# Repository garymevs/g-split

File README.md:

# g-split
A 60%(ish) split keeb (Still waiting on a good name)

Current status: Procrastination
- [x] PCB design
- [x] Case design
- [x] PCB test fit with 3D printed parts
- [ ] Final case design 

Thankies [funkiwinter](https://twitch.tv/funkiwinter) for the cute goat <3

CAD stuff done with [Solid Edge](https://solidedge.siemens.com/en/) and [KiCad](https://www.kicad.org/) (+ other random utilities for hacky workarounds)

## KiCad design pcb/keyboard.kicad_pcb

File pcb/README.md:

# g-split
A 60%(ish) split keeb (Still waiting on a good name)

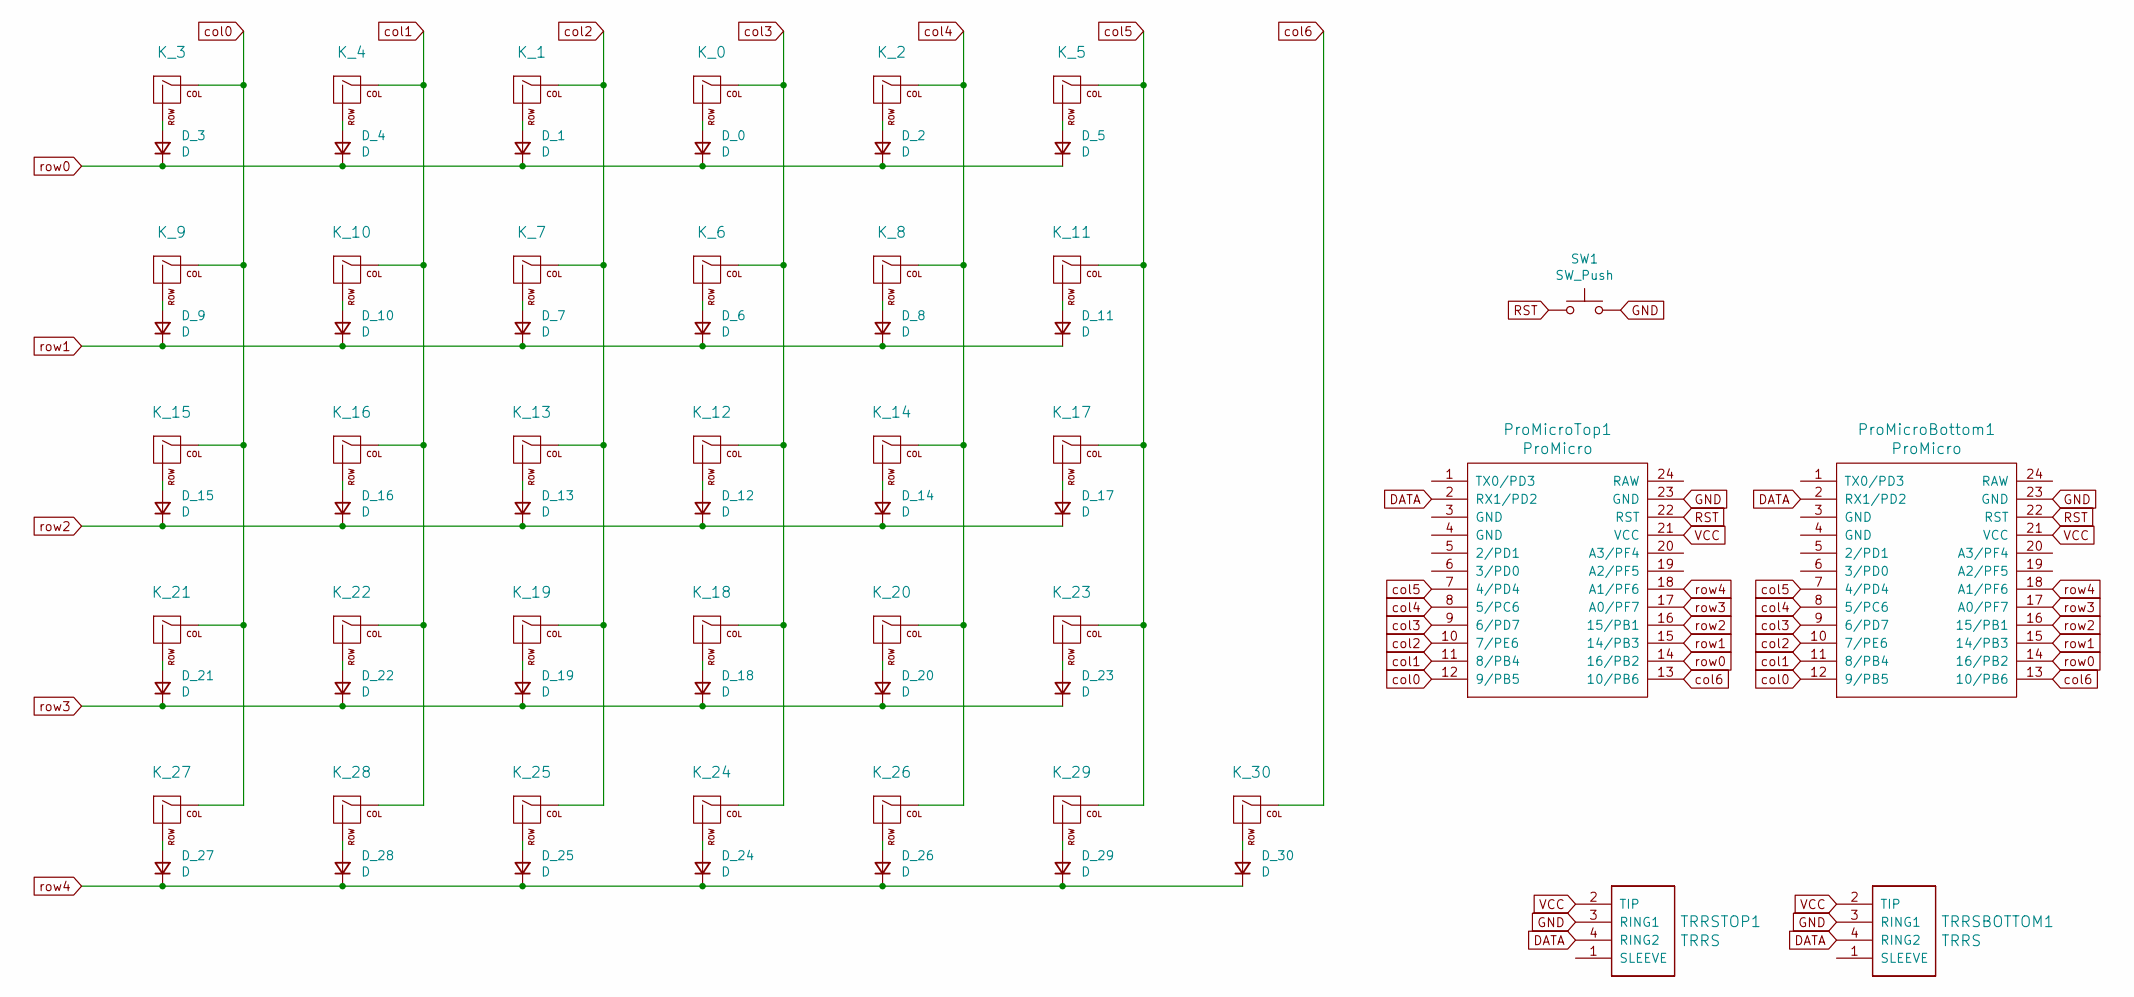
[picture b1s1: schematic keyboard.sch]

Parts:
D_0, D_1, D_2, D_3, D_4, D_5, D_6, D_7, D_8, D_9, D_10, D_11, D_12, D_13, D_14, D_15, D_16, D_17, D_18, D_19, D_20, D_21, D_22, D_23, D_24, D_25, D_26, D_27, D_28, D_29, D_30: D; D_SOD123_axial
K_0, K_1, K_2, K_3, K_4, K_5, K_6, K_7, K_8, K_9, K_10, K_11, K_12, K_13, K_14, K_15, K_16, K_17, K_18, K_19, K_20, K_21, K_22, K_23, K_24, K_25, K_26, K_27, K_28: KEYSW; ReinforcedKailhHotswap
K_29: KEYSW; ReinforcedKailhHotswap-2u-flipped-stab
K_30: KEYSW; ReinforcedKailhHotswap-2u
ProMicroBottom1: ProMicro; ArduinoProMicro
ProMicroTop1: ProMicro; ArduinoProMicro
SW1: SW_Push; SW_PUSH_6mm_H5mm
TRRSBOTTOM1: TRRS; TRRS-PJ-320A
TRRSTOP1: TRRS; TRRS-PJ-320A

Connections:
DATA: ProMicroBottom1.2 (RX1/PD2), ProMicroTop1.2 (RX1/PD2), TRRSBOTTOM1.4 (RING2), TRRSTOP1.4 (RING2)
GND: ProMicroBottom1.23 (GND), ProMicroTop1.23 (GND), SW1.2, TRRSBOTTOM1.3 (RING1), TRRSTOP1.3 (RING1)
unnamed: D_0.2 (A), K_0.2 (ROW)
unnamed: D_1.2 (A), K_1.2 (ROW)
unnamed: D_2.2 (A), K_2.2 (ROW)
unnamed: D_3.2 (A), K_3.2 (ROW)
unnamed: D_4.2 (A), K_4.2 (ROW)
unnamed: D_5.2 (A), K_5.2 (ROW)
unnamed: D_6.2 (A), K_6.2 (ROW)
unnamed: D_7.2 (A), K_7.2 (ROW)
unnamed: D_8.2 (A), K_8.2 (ROW)
unnamed: D_9.2 (A), K_9.2 (ROW)
unnamed: D_10.2 (A), K_10.2 (ROW)
unnamed: D_11.2 (A), K_11.2 (ROW)
unnamed: D_12.2 (A), K_12.2 (ROW)
unnamed: D_13.2 (A), K_13.2 (ROW)
unnamed: D_14.2 (A), K_14.2 (ROW)
unnamed: D_15.2 (A), K_15.2 (ROW)
unnamed: D_16.2 (A), K_16.2 (ROW)
unnamed: D_17.2 (A), K_17.2 (ROW)
unnamed: D_18.2 (A), K_18.2 (ROW)
unnamed: D_19.2 (A), K_19.2 (ROW)
unnamed: D_20.2 (A), K_20.2 (ROW)
unnamed: D_21.2 (A), K_21.2 (ROW)
unnamed: D_22.2 (A), K_22.2 (ROW)
unnamed: D_23.2 (A), K_23.2 (ROW)
unnamed: D_24.2 (A), K_24.2 (ROW)
unnamed: D_25.2 (A), K_25.2 (ROW)
unnamed: D_26.2 (A), K_26.2 (ROW)
unnamed: D_27.2 (A), K_27.2 (ROW)
unnamed: D_28.2 (A), K_28.2 (ROW)
unnamed: D_29.2 (A), K_29.2 (ROW)
unnamed: D_30.2 (A), K_30.2 (ROW)
RST: ProMicroBottom1.22 (RST), ProMicroTop1.22 (RST), SW1.1
VCC: ProMicroBottom1.21 (VCC), ProMicroTop1.21 (VCC), TRRSBOTTOM1.2 (TIP), TRRSTOP1.2 (TIP)
col0: K_3.1 (COL), K_9.1 (COL), K_15.1 (COL), K_21.1 (COL), K_27.1 (COL), ProMicroBottom1.12 (9/PB5), ProMicroTop1.12 (9/PB5)
col1: K_4.1 (COL), K_10.1 (COL), K_16.1 (COL), K_22.1 (COL), K_28.1 (COL), ProMicroBottom1.11 (8/PB4), ProMicroTop1.11 (8/PB4)
col2: K_1.1 (COL), K_7.1 (COL), K_13.1 (COL), K_19.1 (COL), K_25.1 (COL), ProMicroBottom1.10 (7/PE6), ProMicroTop1.10 (7/PE6)
col3: K_0.1 (COL), K_6.1 (COL), K_12.1 (COL), K_18.1 (COL), K_24.1 (COL), ProMicroBottom1.9 (6/PD7), ProMicroTop1.9 (6/PD7)
col4: K_2.1 (COL), K_8.1 (COL), K_14.1 (COL), K_20.1 (COL), K_26.1 (COL), ProMicroBottom1.8 (5/PC6), ProMicroTop1.8 (5/PC6)
col5: K_5.1 (COL), K_11.1 (COL), K_17.1 (COL), K_23.1 (COL), K_29.1 (COL), ProMicroBottom1.7 (4/PD4), ProMicroTop1.7 (4/PD4)
col6: K_30.1 (COL), ProMicroBottom1.13 (10/PB6), ProMicroTop1.13 (10/PB6)
row0: D_0.1 (K), D_1.1 (K), D_2.1 (K), D_3.1 (K), D_4.1 (K), D_5.1 (K), ProMicroBottom1.14 (16/PB2), ProMicroTop1.14 (16/PB2)
row1: D_6.1 (K), D_7.1 (K), D_8.1 (K), D_9.1 (K), D_10.1 (K), D_11.1 (K), ProMicroBottom1.15 (14/PB3), ProMicroTop1.15 (14/PB3)
row2: D_12.1 (K), D_13.1 (K), D_14.1 (K), D_15.1 (K), D_16.1 (K), D_17.1 (K), ProMicroBottom1.16 (15/PB1), ProMicroTop1.16 (15/PB1)
row3: D_18.1 (K), D_19.1 (K), D_20.1 (K), D_21.1 (K), D_22.1 (K), D_23.1 (K), ProMicroBottom1.17 (A0/PF7), ProMicroTop1.17 (A0/PF7)
row4: D_24.1 (K), D_25.1 (K), D_26.1 (K), D_27.1 (K), D_28.1 (K), D_29.1 (K), D_30.1 (K), ProMicroBottom1.18 (A1/PF6), ProMicroTop1.18 (A1/PF6)

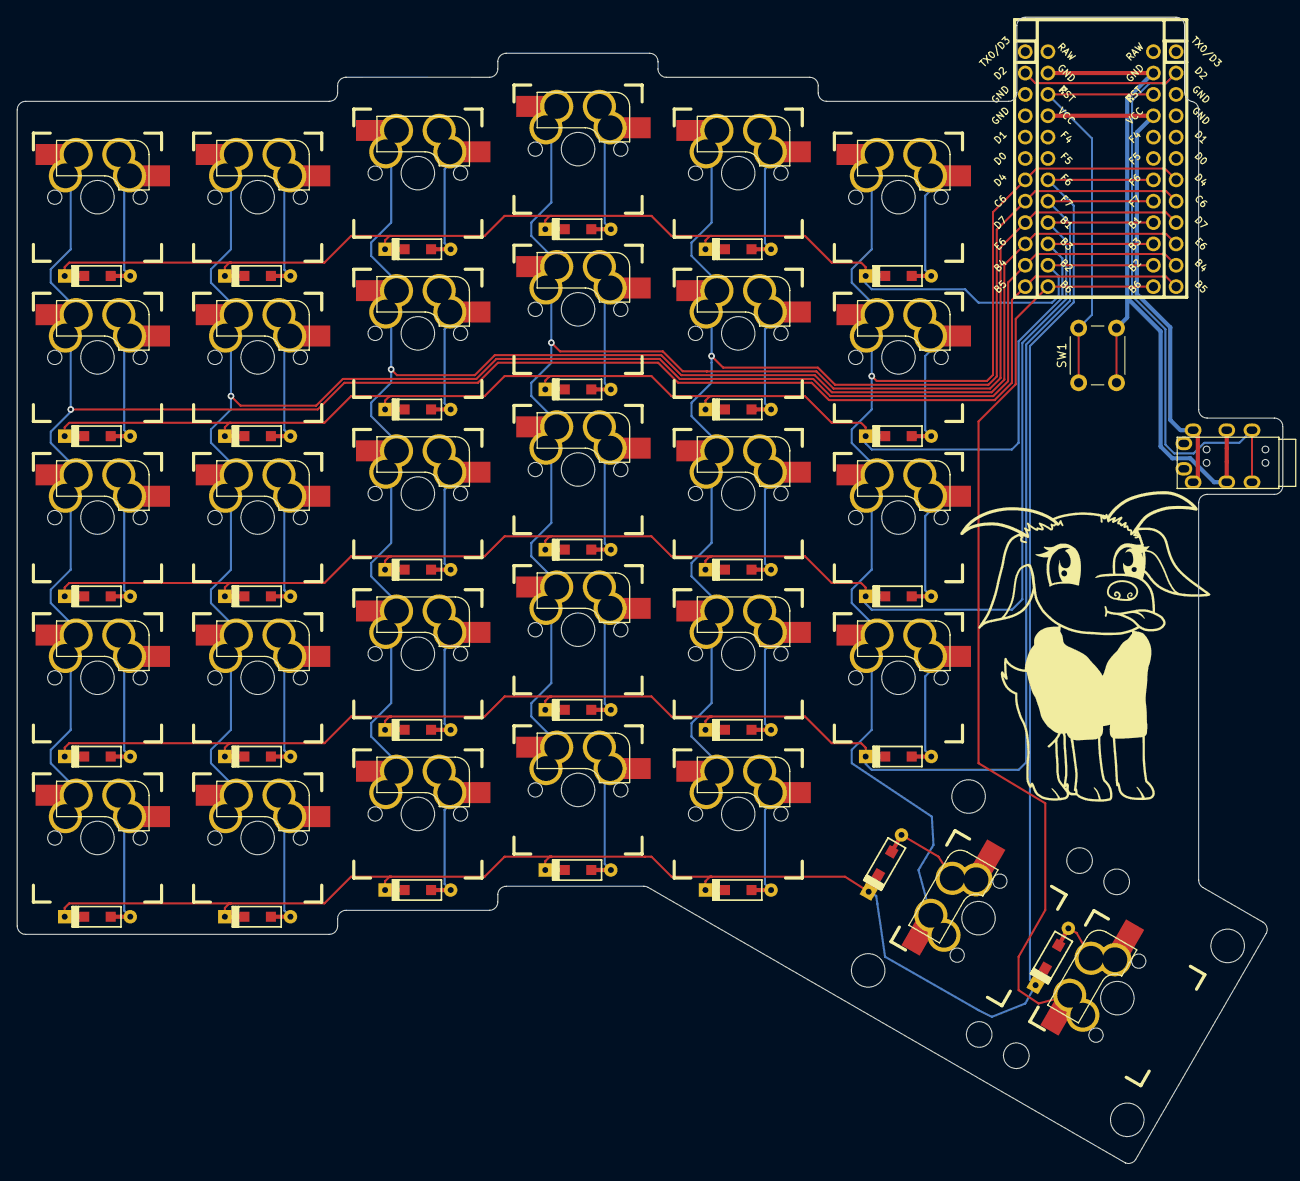
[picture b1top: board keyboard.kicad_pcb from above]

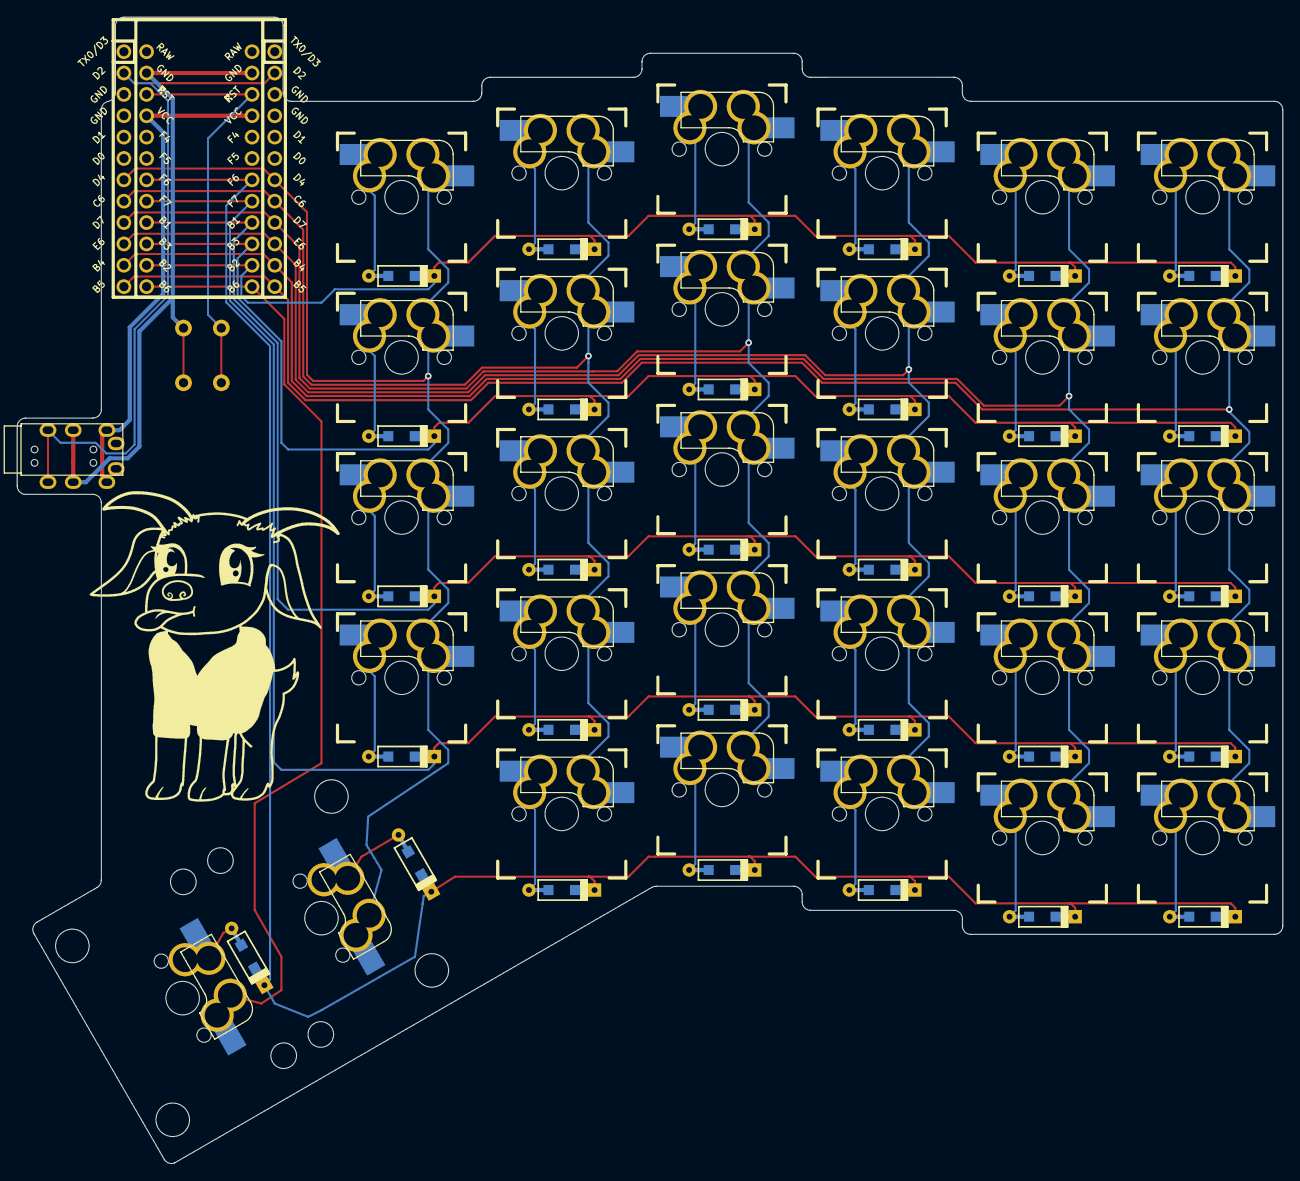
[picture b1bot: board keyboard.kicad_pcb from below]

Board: 2 copper layers, 150.5 x 136.3 mm, 67 parts (33 on the bottom side), 47 nets.

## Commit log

2021-07-25 Fixed file structure
2021-07-25 Moved and updated the readme
2021-07-27 Fixed submodules
2021-07-29 Create LICENSE
2021-08-15 Added traces for rows (kinda important ;_;)
2021-09-25 added extra clearance for the MCU at the top
2021-09-25 split the top of the case for further testing
2021-09-26 Split all the layers out
